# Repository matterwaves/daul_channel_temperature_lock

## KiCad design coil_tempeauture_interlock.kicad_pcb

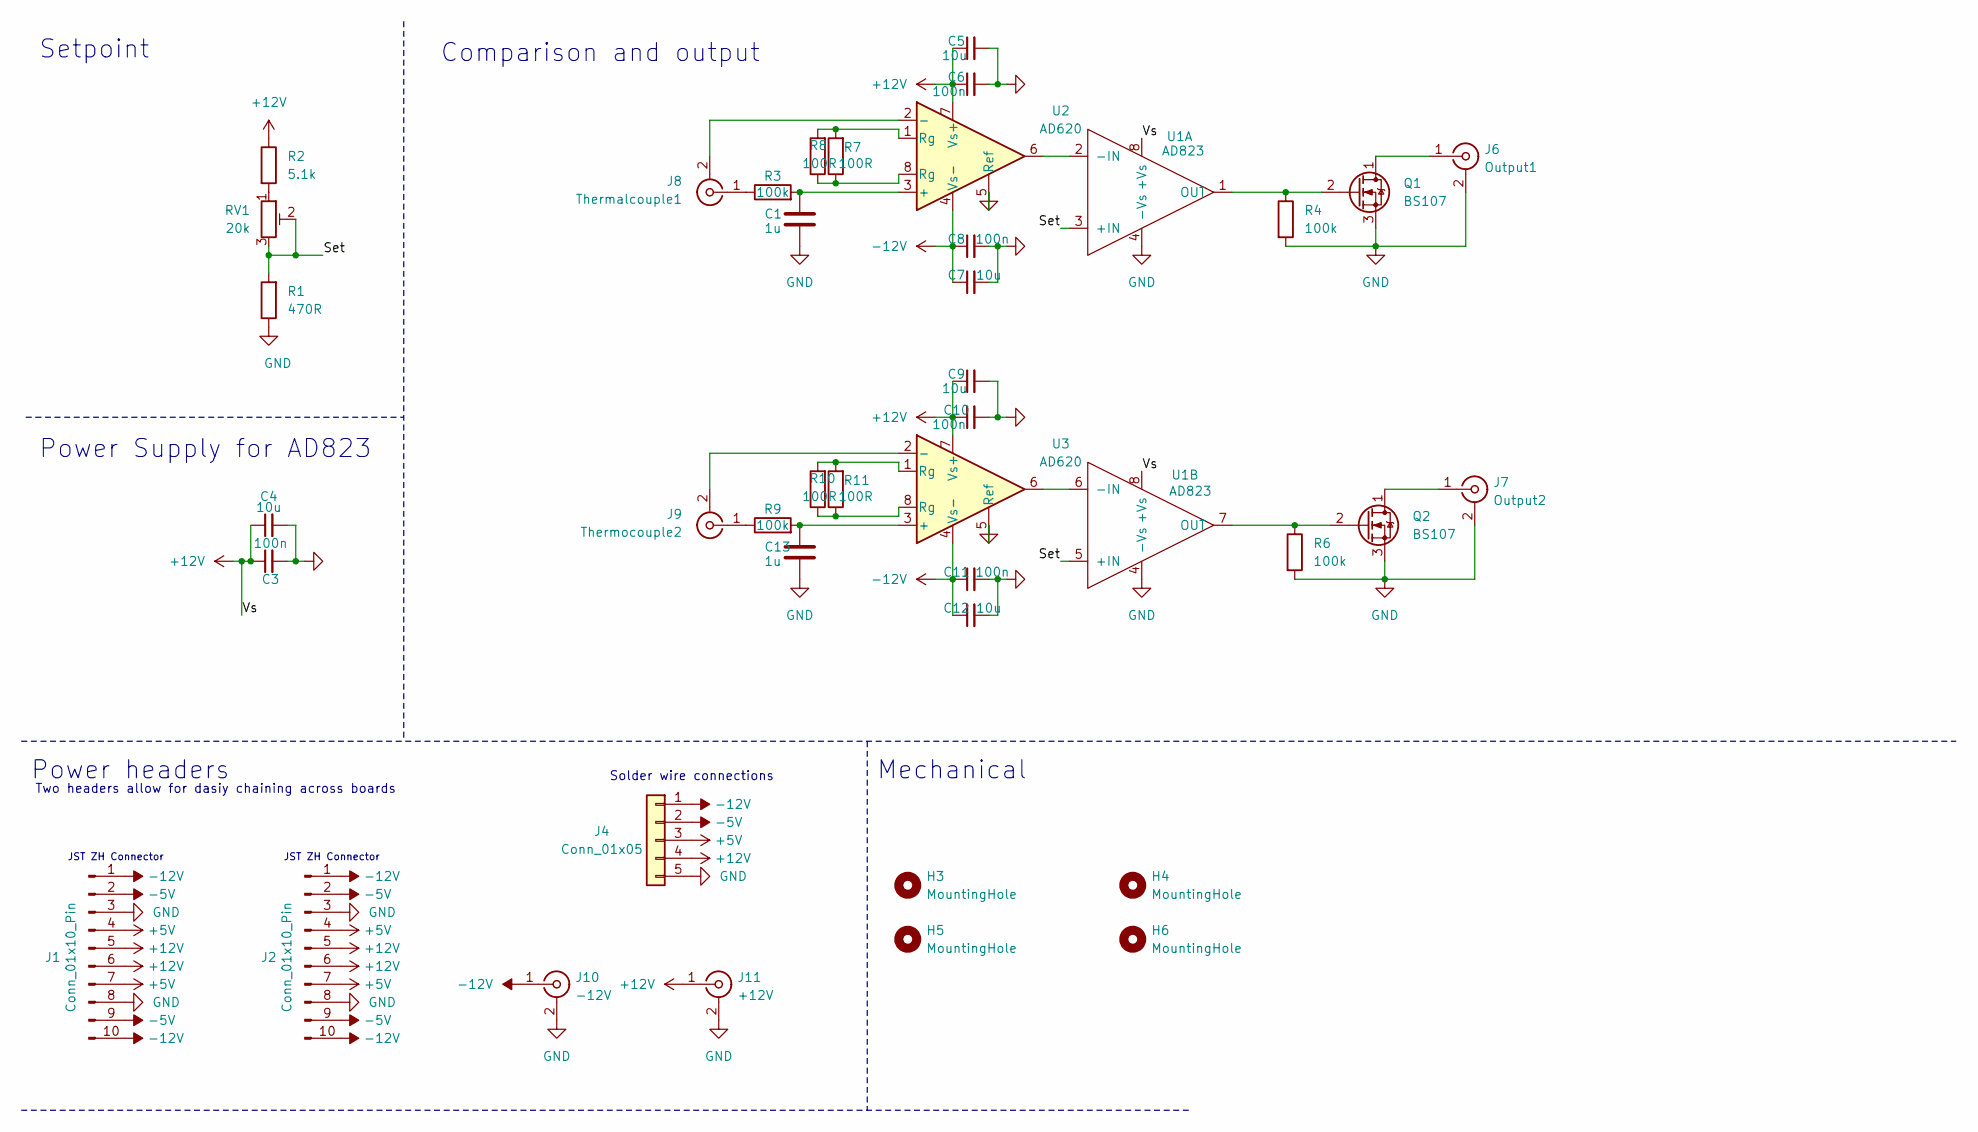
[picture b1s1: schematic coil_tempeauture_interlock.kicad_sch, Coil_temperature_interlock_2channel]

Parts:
C1, C13: 1u; C_Disc_D4.3mm_W1.9mm_P5.00mm; LCSC C2839237
C3, C6, C8, C10, C11: 100n; C_Disc_D4.3mm_W1.9mm_P5.00mm; LCSC C2832508
C4, C5, C7, C9, C12: 10u; C_Disc_D4.3mm_W1.9mm_P5.00mm; LCSC C2761733
H3, H4, H5, H6: MountingHole; MountingHole_3.2mm_M3
J1, J2: Conn_01x10_Pin; JST_ZH_B10B-ZR_1x10_P1.50mm_Vertical; Digikey PN 455-S10B-ZR-ND
J4: Conn_01x05; SolderWire-0.75sqmm_1x05_P4.8mm_D1.25mm_OD2.3mm
J6: Output1; SMA_Molex_73251-1153_EdgeMount_Horizontal; Digikey PN 900-0732511153-ND
J7: Output2; SMA_Molex_73251-1153_EdgeMount_Horizontal; Digikey PN 900-0732511153-ND
J8: Thermalcouple1; SMA_Molex_73251-1153_EdgeMount_Horizontal; Digikey PN 900-0732511153-ND
J9: Thermocouple2; SMA_Molex_73251-1153_EdgeMount_Horizontal; Digikey PN 900-0732511153-ND
J10: -12V; SMA_Molex_73251-1153_EdgeMount_Horizontal; Digikey PN 900-0732511153-ND
J11: +12V; SMA_Molex_73251-1153_EdgeMount_Horizontal; Digikey PN 900-0732511153-ND
Q1, Q2: BS107; TO-92_Inline; LCSC C156337
R1: 470R; R_Axial_DIN0207_L6.3mm_D2.5mm_P10.16mm_Horizontal; LCSC C119317
R2: 5.1k; R_Axial_DIN0207_L6.3mm_D2.5mm_P10.16mm_Horizontal; LCSC C58591
R3, R4, R6, R9: 100k; R_Axial_DIN0207_L6.3mm_D2.5mm_P10.16mm_Horizontal; LCSC C2843019
R7, R8, R10, R11: 100R; R_Axial_DIN0207_L6.3mm_D2.5mm_P10.16mm_Horizontal; LCSC C57438
RV1: 20k; Potentiometer_Bourns_3296W_Vertical; LCSC C34845
U1: AD823; DIP-8_W7.62mm_Socket_LongPads
U2, U3: AD620; DIP-8_W7.62mm_Socket_LongPads

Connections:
+5V: J1.4, J1.7, J2.4, J2.7, J4.3
+12V: C3.1, C4.1, C5.1, C6.1, C9.1, C10.1, J1.5, J1.6, J2.5, J2.6, J4.4, J11.1 (In), R2.1, U1.8 (+Vs), U2.7 (Vs+), U3.7 (Vs+)
-5V: J1.2, J1.9, J2.2, J2.9, J4.2
-12V: C7.1, C8.1, C11.1, C12.1, J1.1, J1.10, J2.1, J2.10, J4.1, J10.1 (In), U2.4 (Vs-), U3.4 (Vs-)
/Set: R1.2, RV1.2, RV1.3, U1.3 (+IN), U1.5 (+IN)
GND: C1.2, C3.2, C4.2, C5.2, C6.2, C7.2, C8.2, C9.2, C10.2, C11.2, C12.2, C13.2, J1.3, J1.8, J2.3, J2.8, J4.5, J6.2 (Ext), J7.2 (Ext), J10.2 (Ext), J11.2 (Ext), Q1.3 (S), Q2.3 (S), R1.1, R4.2, R6.2, U1.4 (-Vs), U2.5 (Ref), U3.5 (Ref)
unnamed: J6.1 (In), Q1.1 (D)
unnamed: J7.1 (In), Q2.1 (D)
unnamed: J8.2 (Ext), U2.2 (-)
unnamed: J8.1 (In), R3.1
unnamed: J9.2 (Ext), U3.2 (-)
unnamed: J9.1 (In), R9.1
unnamed: Q1.2 (G), R4.1, U1.1 (OUT)
unnamed: Q2.2 (G), R6.1, U1.7 (OUT)
unnamed: R2.2, RV1.1
unnamed: R7.1, R8.1, U2.8 (Rg)
unnamed: R7.2, R8.2, U2.1 (Rg)
unnamed: R10.1, R11.1, U3.8 (Rg)
unnamed: R10.2, R11.2, U3.1 (Rg)
unnamed: U1.2 (-IN), U2.6
unnamed: U1.6 (-IN), U3.6
unnamed: C1.1, R3.2, U2.3 (+)
unnamed: C13.1, R9.2, U3.3 (+)

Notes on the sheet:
Solder wire connections
Setpoint
Mechanical
JST ZH Connector
Comparison and output
Power headers
Two headers allow for dasiy chaining across boards
Power Supply for AD823

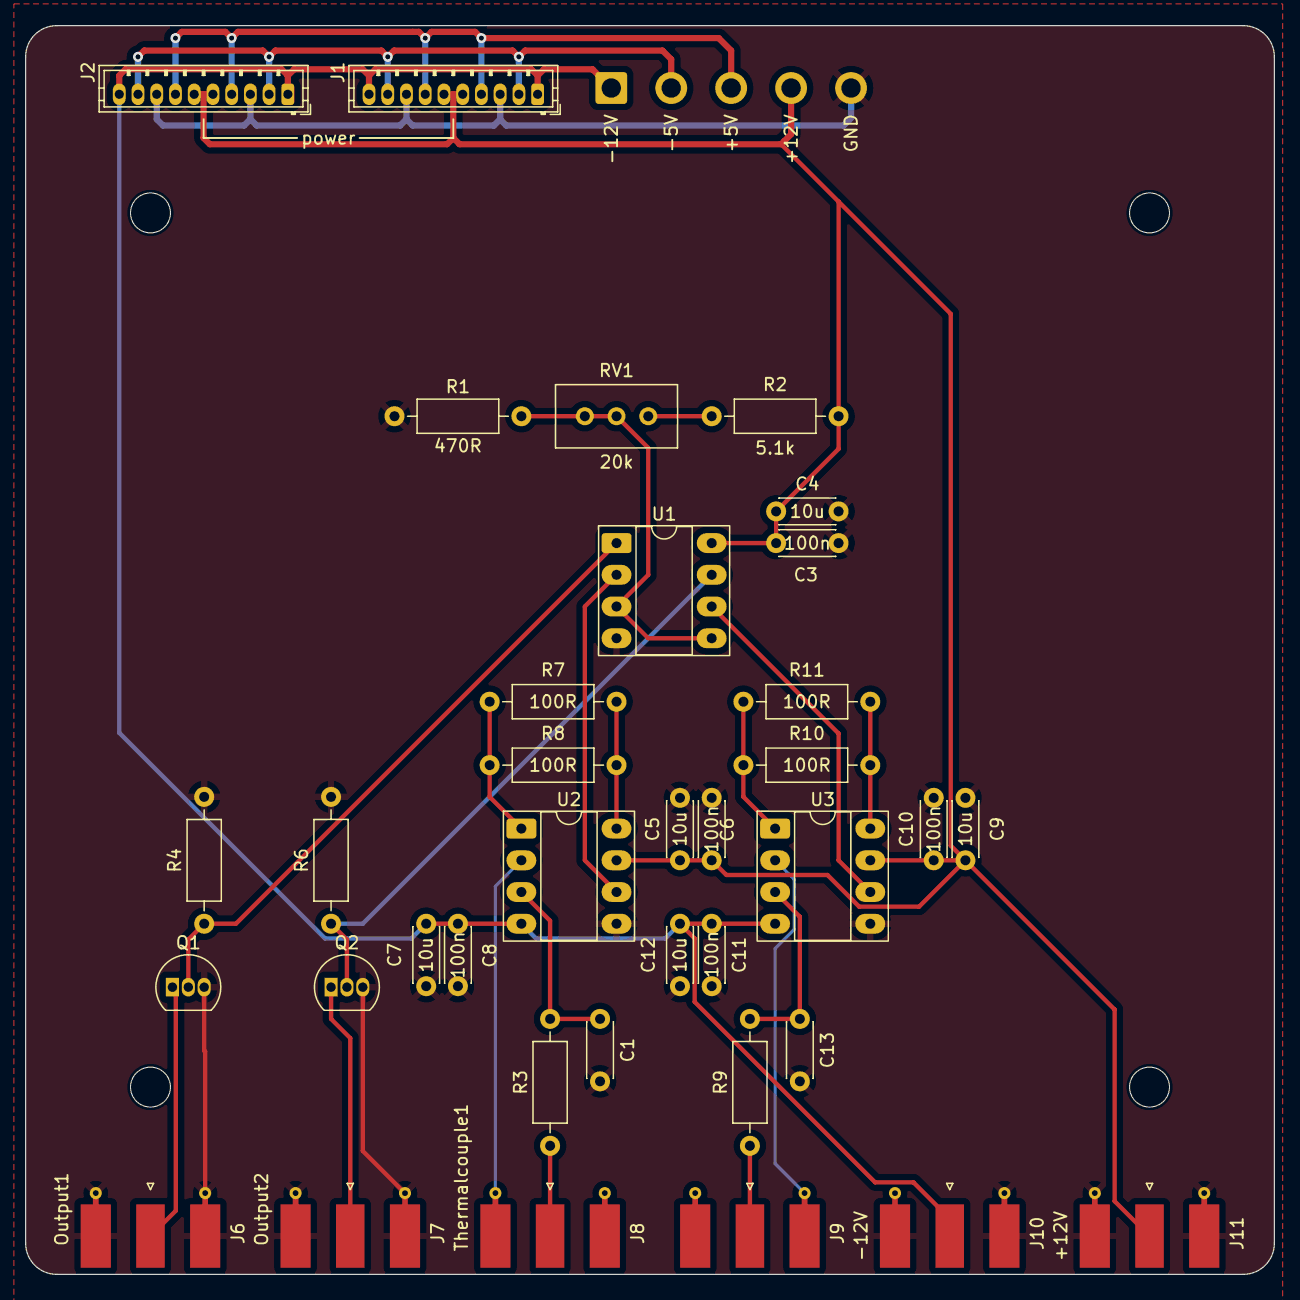
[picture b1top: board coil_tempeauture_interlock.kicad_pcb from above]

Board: 4 copper layers, 100.0 x 100.0 mm, 41 parts (0 on the bottom side), 23 nets.

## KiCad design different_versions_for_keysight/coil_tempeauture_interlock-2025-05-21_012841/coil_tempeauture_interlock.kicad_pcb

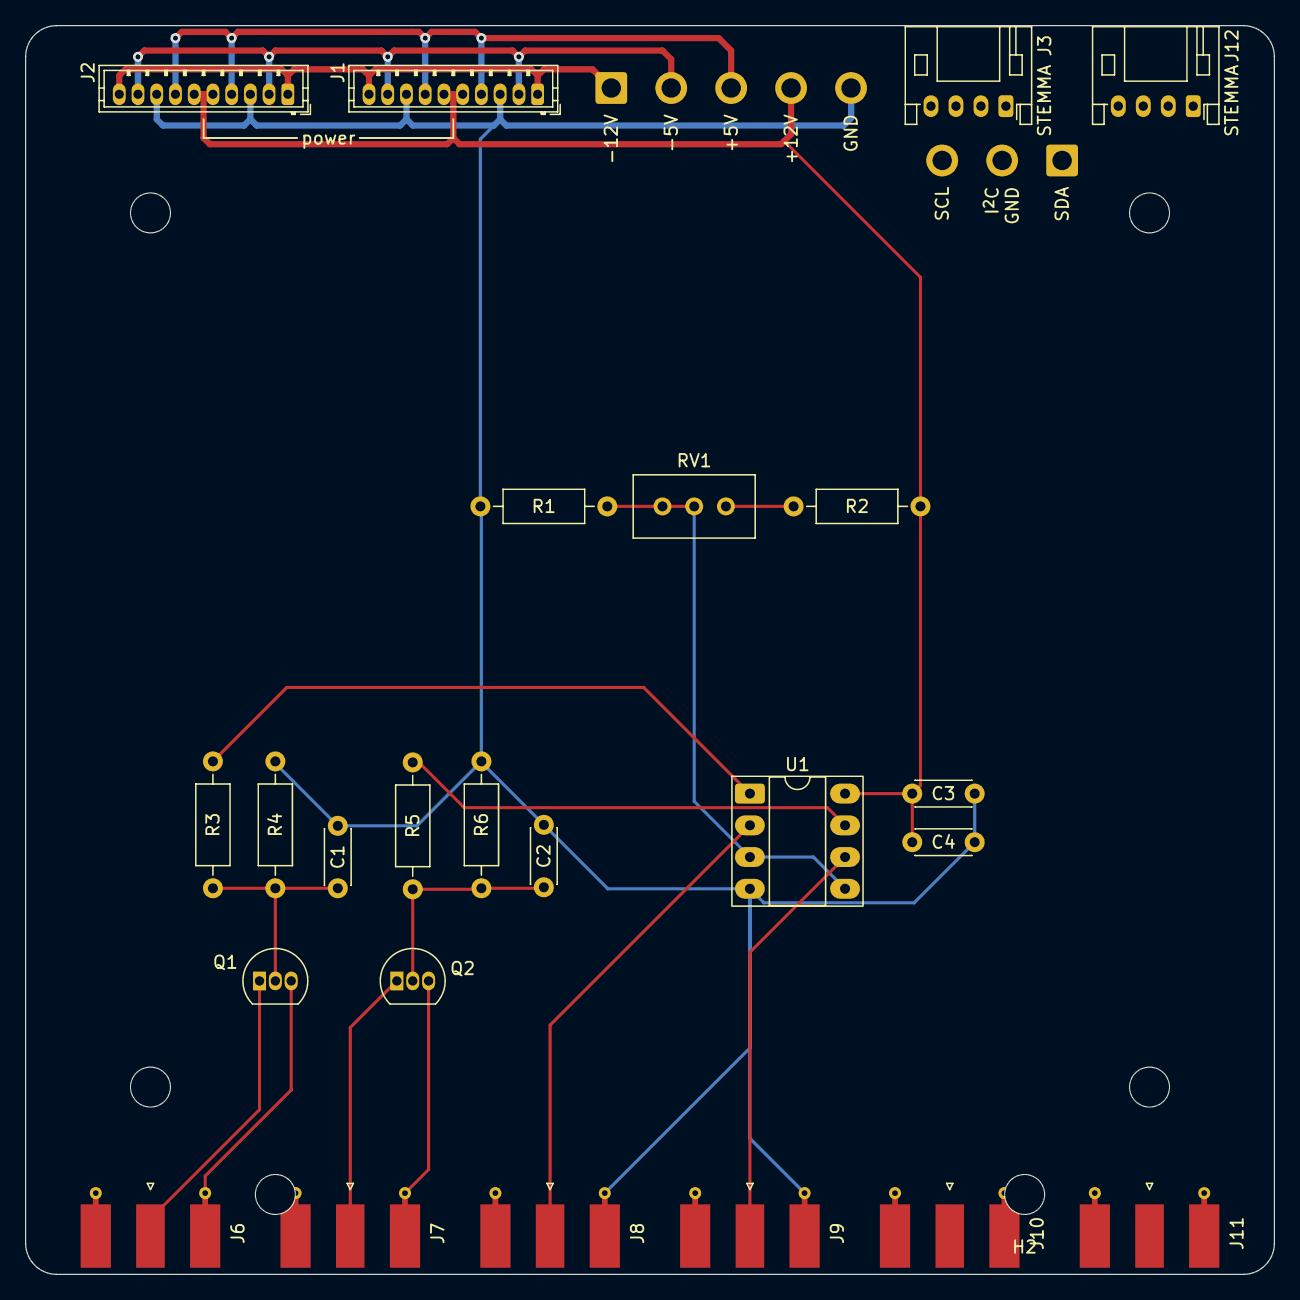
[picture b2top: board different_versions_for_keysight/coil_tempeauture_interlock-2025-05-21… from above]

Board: 4 copper layers, 100.0 x 100.0 mm, 32 parts (0 on the bottom side), 19 nets.

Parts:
C1, C2: 1u; C_Disc_D4.3mm_W1.9mm_P5.00mm
C3: 100n; C_Disc_D4.3mm_W1.9mm_P5.00mm
C4: 10u; C_Disc_D4.3mm_W1.9mm_P5.00mm
H1, H2: Keystone Electronics 621; Keystone 621
H3, H4, H5, H6: MountingHole; MountingHole_3.2mm_M3
J1, J2: Conn_01x10_Pin; JST_ZH_B10B-ZR_1x10_P1.50mm_Vertical
J3, J12: Conn_01x04_Pin; JST_PH_S4B-PH-K_1x04_P2.00mm_Horizontal
J4: Conn_01x05; SolderWire-0.75sqmm_1x05_P4.8mm_D1.25mm_OD2.3mm
J5: Conn_01x03; SolderWire-0.75sqmm_1x03_P4.8mm_D1.25mm_OD2.3mm
J6, J7, J8, J9, J10, J11: Conn_Coaxial; SMA_Molex_73251-1153_EdgeMount_Horizontal
Q1, Q2: BS107; TO-92_Inline
R1: 5R; R_Axial_DIN0207_L6.3mm_D2.5mm_P10.16mm_Horizontal
R2: 47k; R_Axial_DIN0207_L6.3mm_D2.5mm_P10.16mm_Horizontal
R3, R4, R5, R6: 100k; R_Axial_DIN0207_L6.3mm_D2.5mm_P10.16mm_Horizontal
RV1: 100k; Potentiometer_Bourns_3296W_Vertical
U1: AD823; DIP-8_W7.62mm_Socket_LongPads

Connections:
+5V: J1.4, J1.7, J2.4, J2.7, J4.3
+12V: C3.1, C4.1, J1.5, J1.6, J2.5, J2.6, J4.4, R2.1, U1.8 (+Vs)
-5V: J1.2, J1.9, J2.2, J2.9, J4.2
-12V: J1.1, J1.10, J2.1, J2.10, J4.1
/I2C_SCL: J3.1, J5.3, J12.1
/I2C_SDA: J3.2, J5.1, J12.2
/Ref: R1.2, RV1.2, RV1.3, U1.3 (+IN), U1.5 (+IN)
GND: C1.2, C2.2, C3.2, C4.2, J1.3, J1.8, J2.3, J2.8, J4.5, J6.2 (Ext), J7.2 (Ext), J8.2 (Ext), J9.2 (Ext), Q1.3 (S), Q2.3 (S), R1.1, R4.2, R6.2, U1.4 (-Vs)
GNDS: J3.4, J5.2, J12.4
unnamed: J6.1 (In), Q1.1 (D)
unnamed: J7.1 (In), Q2.1 (D)
unnamed: J8.1 (In), U1.2 (-IN)
unnamed: J9.1 (In), U1.6 (-IN)
unnamed: C1.1, Q1.2 (G), R3.2, R4.1
unnamed: C2.1, Q2.2 (G), R5.2, R6.1
unnamed: R2.2, RV1.1
unnamed: R3.1, U1.1 (OUT)
unnamed: R5.1, U1.7 (OUT)
VBUS: J3.3, J12.3

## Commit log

2025-05-20 initial
2025-06-08 update interlock with AD620
2025-06-20 add the current using one for Keysight
2025-06-20 isolate thermocouple input
